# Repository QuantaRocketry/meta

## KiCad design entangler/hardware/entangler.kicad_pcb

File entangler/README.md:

# Entangler

## Setup

```bash
sudo dnf5 group install development-tools

sudo dnf install \
    SDL2-devel # if you want to run the simulator
```

## Run the simulation

```bash
cargo run -p entangler-simulation
```

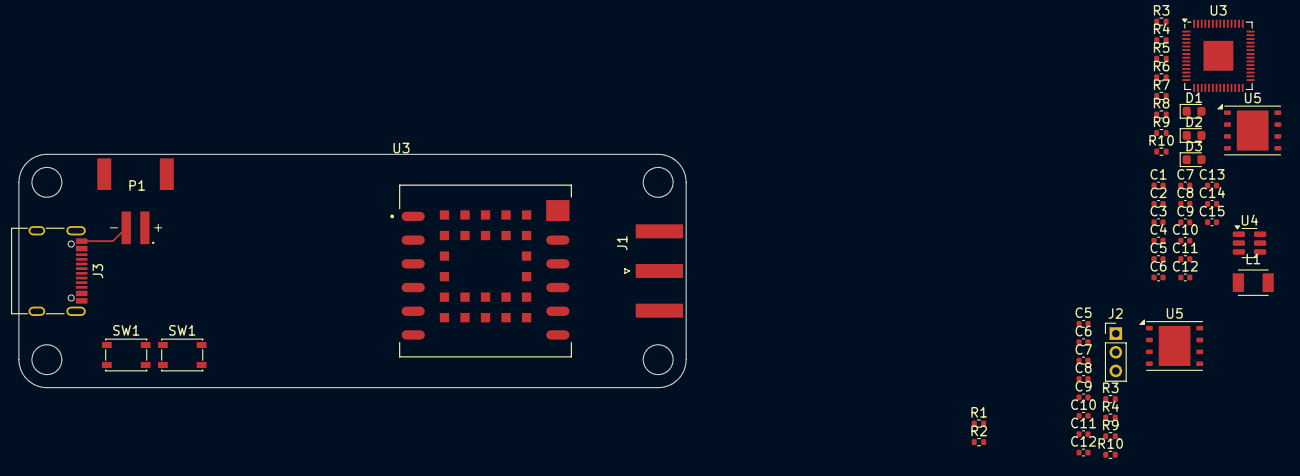
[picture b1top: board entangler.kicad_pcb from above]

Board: 4 copper layers, 71.5 x 25.0 mm, 53 parts (1 on the bottom side), 38 nets.

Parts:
C1, C8, C8#2, C9, C9#2, C11, C11#2, C12, C12#2, C14: 100nf; C_0402_1005Metric
C2, C3: 22uf; C_0402_1005Metric
C4, C13, C15: 10uf; C_0402_1005Metric
C5, C5#2, C6, C6#2: 15pf; C_0402_1005Metric
C7, C7#2, C10, C10#2: 2.2uf; C_0402_1005Metric
D1, D2, D3: LED; LED_0603_1608Metric
J1: Conn_Coaxial_Small; SMA_Amphenol_132289_EdgeMount
J2: Conn_01x03; PinHeader_1x03_P2.00mm_Vertical
J3: USB-7010ASV; USB_C_Receptacle_G-Switch_GT-USB-7010ASV
L1: 10uh; L_TDK_NLV32_3.2x2.5mm
P1: S2B-PH-SM4-TB; JST_S2B-PH-SM4-TB
R1, R2: 5.1kr; R_0402_1005Metric
R3, R3#2, R4, R4#2: 27r; R_0402_1005Metric
R5, R6, R8: 66.5r; R_0402_1005Metric
R7: 10kr; R_0402_1005Metric
R9, R9#2, R10, R10#2: 1kr; R_0402_1005Metric
SW1, SW1#2: Push_Button; SW_SPST_PTS810
U2: RFM95W-868S2; HOPERF_RFM9XW_SMD
U3: RP2040; QFN-56-1EP_7x7mm_P0.4mm_EP3.2x3.2mm
U3#2: LC86G; XCVR_LC86G
U4: AP63203WU; TSOT-23-6
U5, U5#2: W25Q32JVZP; WSON-8-1EP_6x5mm_P1.27mm_EP3.4x4.3mm

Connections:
+1V1: C7.1, C7#2.1, C8.1, C8#2.1, C12.1, C12#2.1, U3.23 (DVDD), U3.45 (VREG_VOUT), U3.50 (DVDD)
+3V3: C2.2, C3.2, C9.1, C9#2.1, C10.1, C10#2.1, C11.1, C11#2.1, C13.1, C14.1, C15.1, L1.2, R5.1, R7.1, U2.13 (3.3V), U3.1 (IOVDD), U3.10 (IOVDD), U3.22 (IOVDD), U3.26 (RUN), U3.33 (IOVDD), U3.42 (IOVDD), U3.43 (ADC_AVDD), U3.44 (VREG_IN), U3.48 (USB_VDD), U3.49 (IOVDD), U3#2.4 (VCC), U3#2.5 (V_BCKP), U4.1 (FB), U5.8 (VCC), U5#2.8 (VCC)
/MCU/QSPI_SS: R9.1, U5.1 (~CS)
CSN: U2.5 (NSS), U3.28 (GPIO17)
GND: C2.1, C3.1, C4.2, C5.2, C5#2.2, C6.2, C6#2.2, C7.2, C7#2.2, C8.2, C8#2.2, C9.2, C9#2.2, C10.2, C10#2.2, C11.2, C11#2.2, C12.2, C12#2.2, C13.2, C14.2, C15.2, D1.1 (K), D2.1 (K), D3.1 (K), J1.2 (Ext), J2.2, J3.A1 (GND), J3.A12 (GND), J3.B1 (GND), J3.B12 (GND), P1.2, R1.2, R2.2, SW1.1, SW1#2.1, U2.1 (GND), U2.8 (GND), U2.10 (GND), U3.19 (TESTEN), U3.57 (GND), U3#2.3 (GND), U3#2.12 (GND), U3#2.13 (GND), U3#2.14 (GND), U3#2.15 (GND), U3#2.16 (GND), U3#2.17 (GND), U3#2.18 (GND), U3#2.19 (GND), U3#2.20 (GND), U3#2.21 (GND), U3#2.22 (GND), U3#2.23 (GND), U3#2.24 (GND), U3#2.25 (GND), U3#2.26 (GND), U3#2.27 (GND), U3#2.28 (GND), U3#2.29 (GND), U3#2.30 (GND), U3#2.31 (GND), U3#2.32 (GND), U3#2.33 (GND), U3#2.34 (GND), U3#2.35 (GND), U3#2.36 (GND), U4.4 (GND), U5.4 (GND), U5#2.4 (GND)
GPS_1PPS: R8.1, U3#2.6 (1PPS)
GPS_RST: R7.2, U3.4 (GPIO2), U3#2.10 (~RESET)
LED_1: R6.1, U3.37 (GPIO25)
MCU_RX: U3.3 (GPIO1), U3#2.2 (TXD)
MCU_TX: U3.2 (GPIO0), U3#2.1 (RXD)
MISO: U2.2 (MISO), U3.27 (GPIO16)
MOSI: U2.3 (MOSI), U3.30 (GPIO19)
unnamed: D1.2 (A), R5.2
unnamed: D2.2 (A), R6.2
unnamed: D3.2 (A), R8.2
unnamed: J1.1 (In), U2.9 (ANT)
unnamed: J3.A5 (CC1), R1.1
unnamed: J3.B5 (CC2), R2.1
unnamed: R9.2, R9#2.2, SW1.2, SW1#2.2
unnamed: U3.52 (QSPI_SCLK), U5#2.6 (CLK)
unnamed: U3.53 (QSPI_SD0), U5#2.5 (DI(IO0))
unnamed: U3.55 (QSPI_SD1), U5#2.2 (DO(IO1))
unnamed: U3.54 (QSPI_SD2), U5#2.3 (IO2)
unnamed: U3.51 (QSPI_SD3), U5#2.7 (IO3)
unnamed: R9#2.1, U3.56 (QSPI_SS), U5#2.1 (~CS)
unnamed: R4#2.2, U3.46 (USB_DM)
unnamed: R3#2.2, U3.47 (USB_DP)
unnamed: C1.2, L1.1, U4.6 (BST)
unnamed: C1.1, U4.5 (SW)
unnamed: C5.1, C5#2.1, R10.2, R10#2.2
RF_DIO: U2.14 (DIO0), U3.7 (GPIO5)
RF_RST: U2.6 (RESET), U3.9 (GPIO7)
SCK: U2.4 (SCK), U3.29 (GPIO18)
USB_D+: J3.A6 (D+), J3.B6 (D+), R3#2.1
USB_D-: J3.A7 (D-), J3.B7 (D-), R4#2.1
VBAT: C4.1, J3.A4 (VBUS), J3.A9 (VBUS), J3.B4 (VBUS), J3.B9 (VBUS), P1.1, U4.2 (EN), U4.3 (IN)
XIN: C6.1, U3.20 (XIN)
XOUT: R10.1, U3.21 (XOUT)

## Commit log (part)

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2025-07-30 compiling
2025-08-18 flake update
2025-08-18 add hardware
2025-09-23 Use runners
2025-09-28 Start entangler pcb
2025-10-09 Progress towards v0.2
2025-10-12 Update libs + adding more pins
2025-10-28 Use protobuf instead of zerocopy
2025-10-29 Better testing
2025-11-16 Add entangler workspace + sim for entangler UI
2025-11-16 Add qcp build dep
2025-11-16 Move generic display to lib + make more generic
2025-11-18 entangler: Half complete radar display
2025-11-19 Mid-port to buoyant
2025-11-26 Move waveshare to esp32 waveshare
    preparing for rp waveshare
2025-11-27 Working esp embassy build
2025-11-28 start on mipidsi
2025-11-28 functional screen clearing with mipidsi
2025-12-21 Functional (?) esp display
2025-12-23 Mock visualiser for filter performance
2025-12-24 Add egui ctrl
    Use kiss3d::main instead of smol
    Track rocket with camera
2025-12-25 Quite broken + slint
2026-02-03 Add noise-effected path
2026-02-16 Add nmea-stream
2026-04-03 Functional uf2
2026-04-08 Functional rtic with generic tasks and usb echo
2026-04-19 Use cargo-uf2 instead of uf2 script
2026-04-19 Use cargo embed for defmt and initial working oled
2026-05-10 use esp2flash for uf2 on run
